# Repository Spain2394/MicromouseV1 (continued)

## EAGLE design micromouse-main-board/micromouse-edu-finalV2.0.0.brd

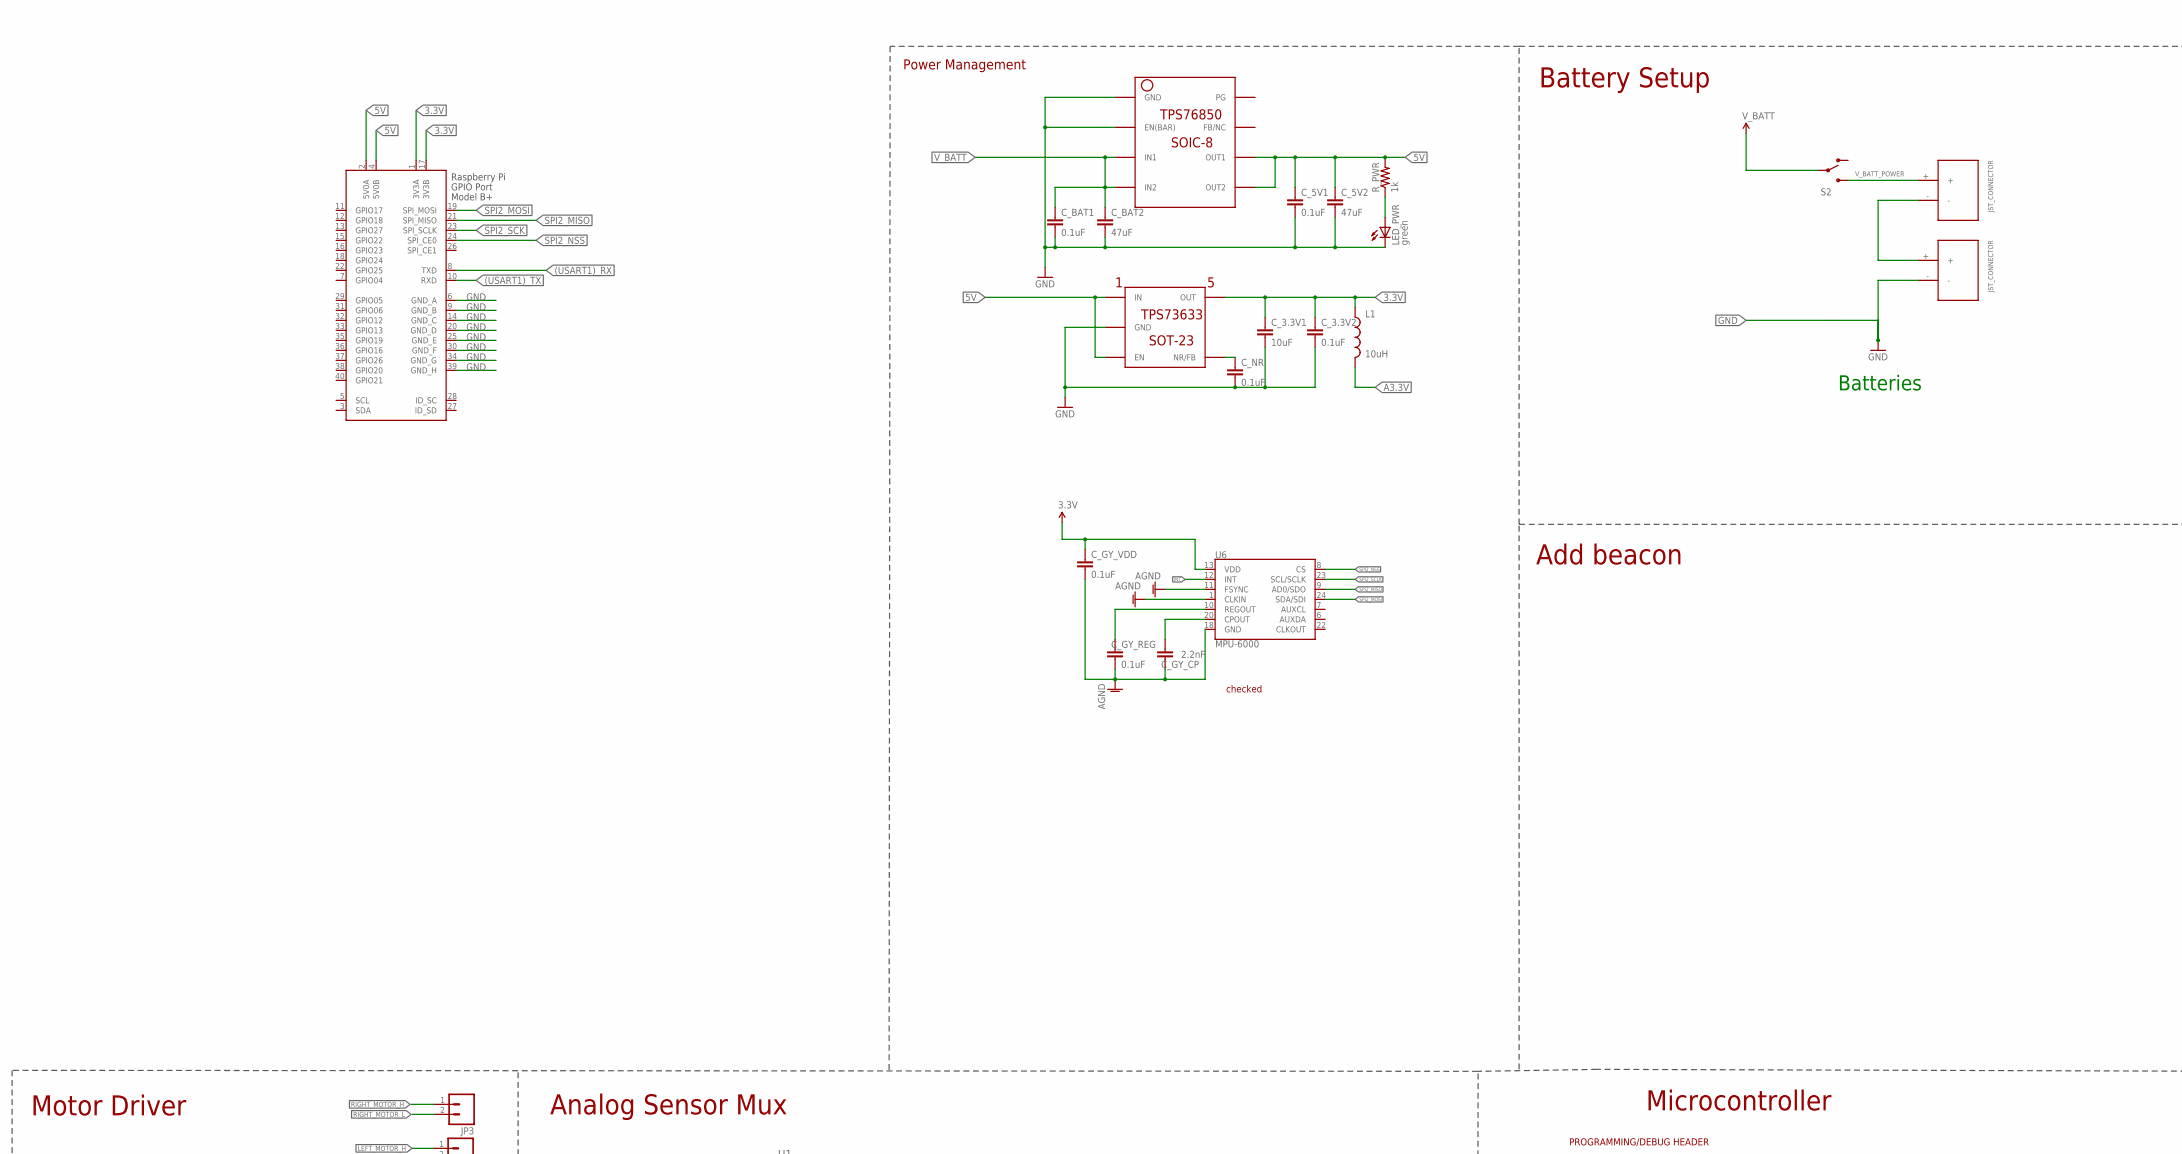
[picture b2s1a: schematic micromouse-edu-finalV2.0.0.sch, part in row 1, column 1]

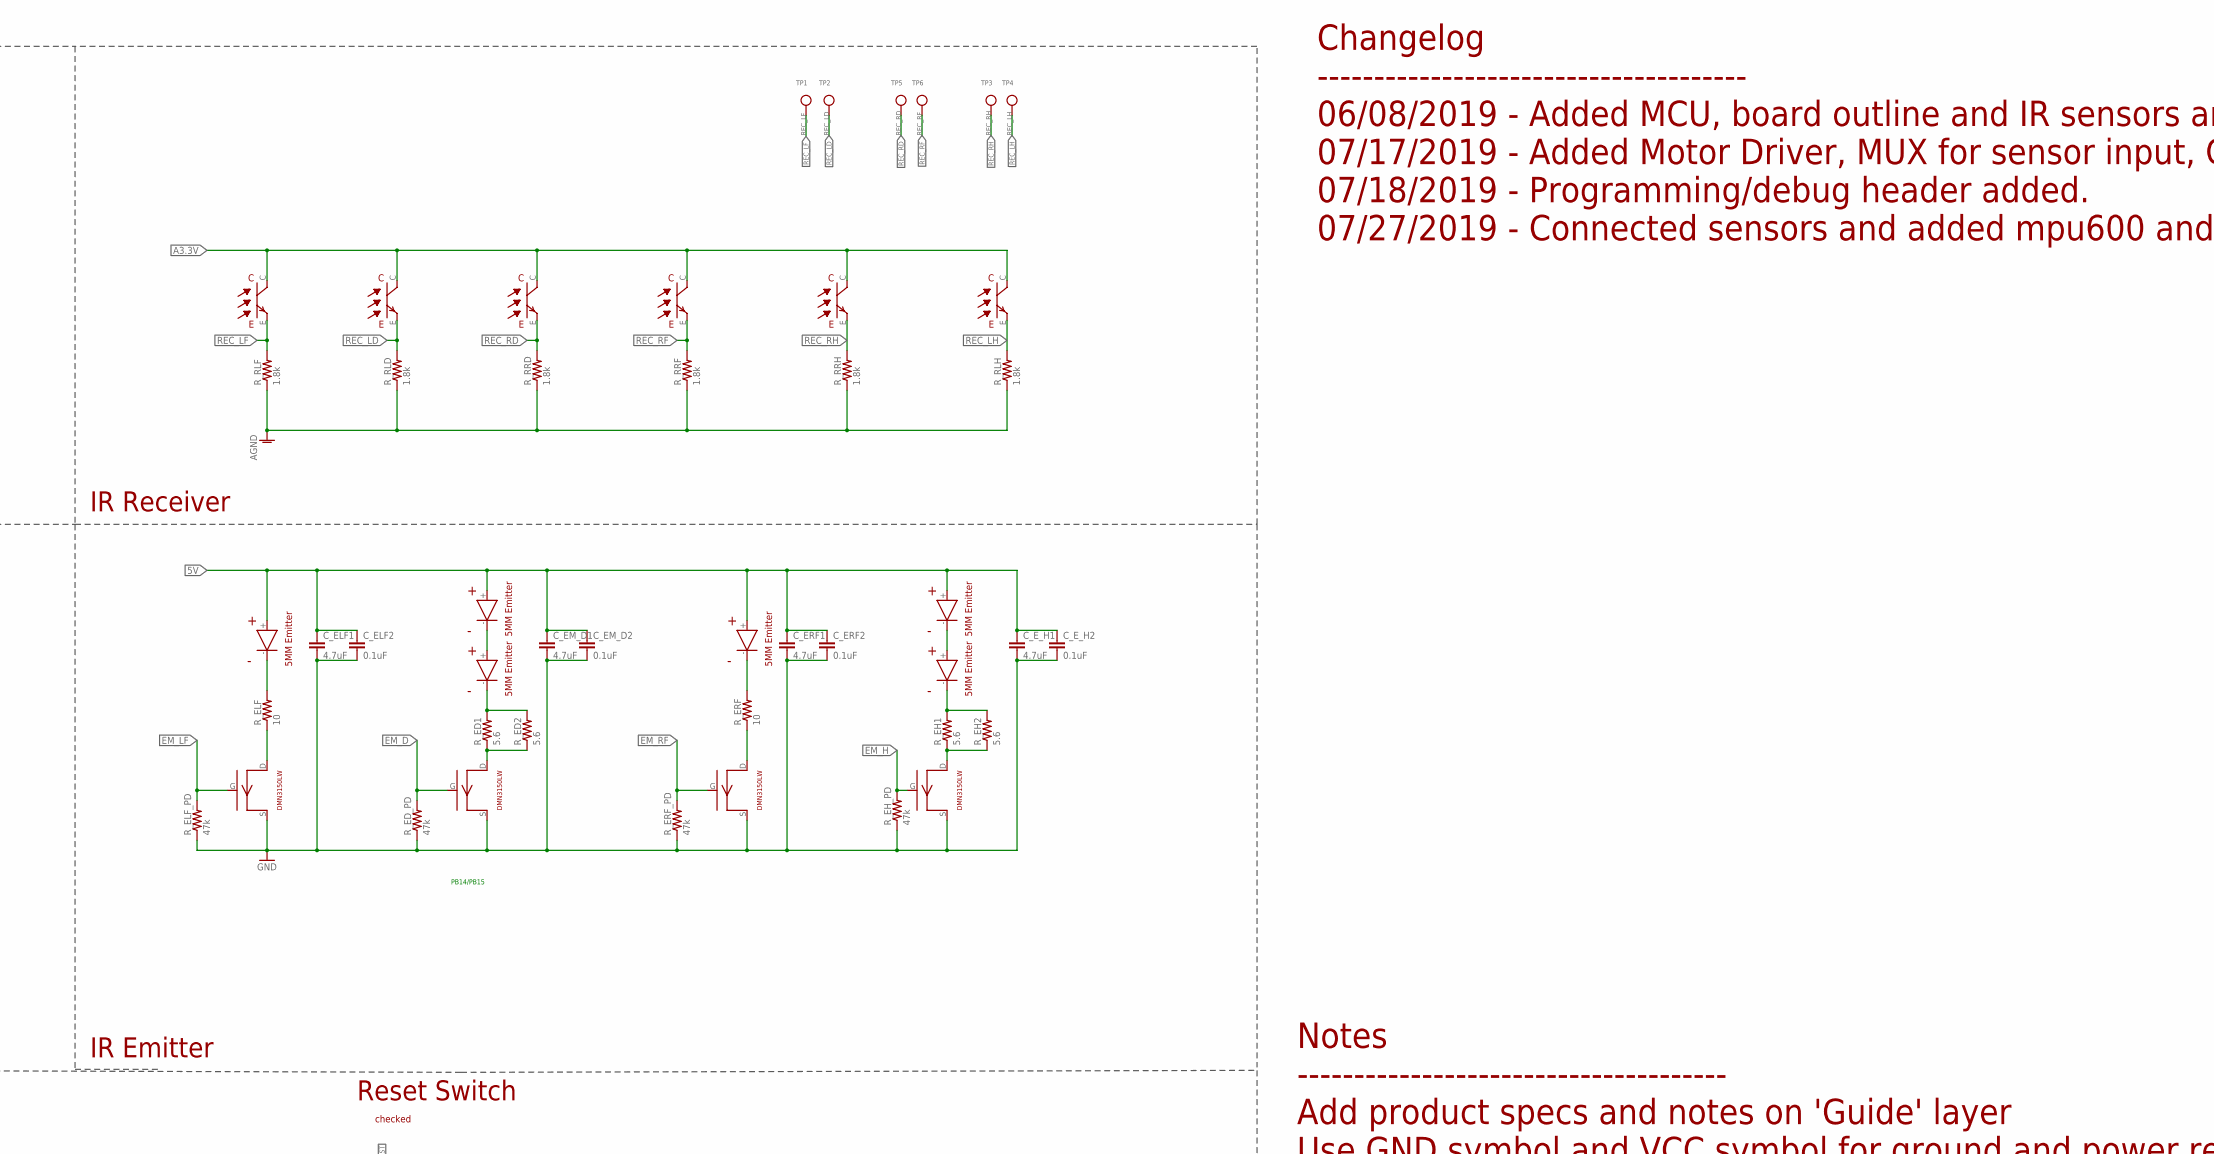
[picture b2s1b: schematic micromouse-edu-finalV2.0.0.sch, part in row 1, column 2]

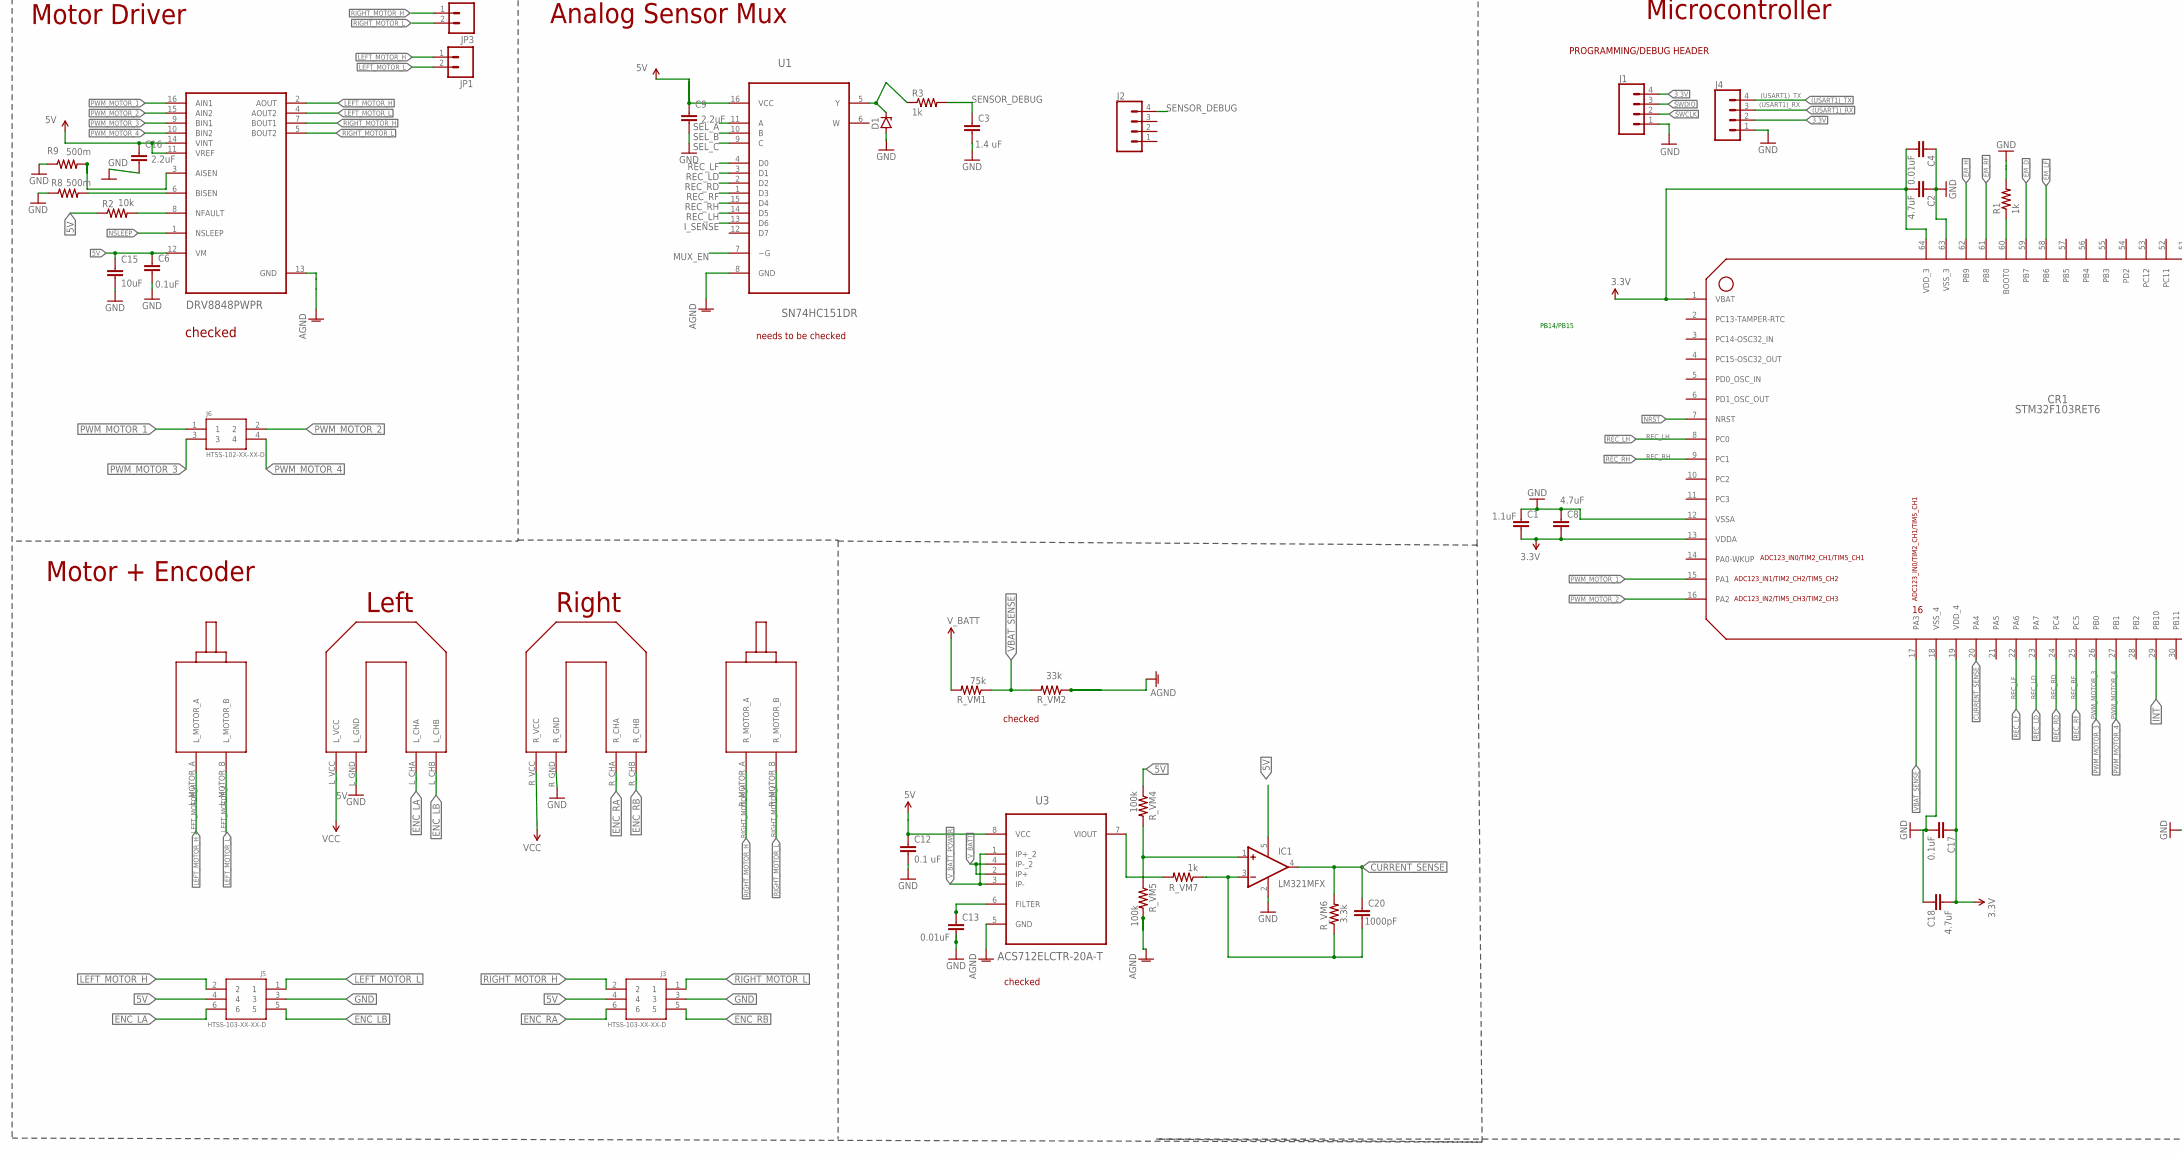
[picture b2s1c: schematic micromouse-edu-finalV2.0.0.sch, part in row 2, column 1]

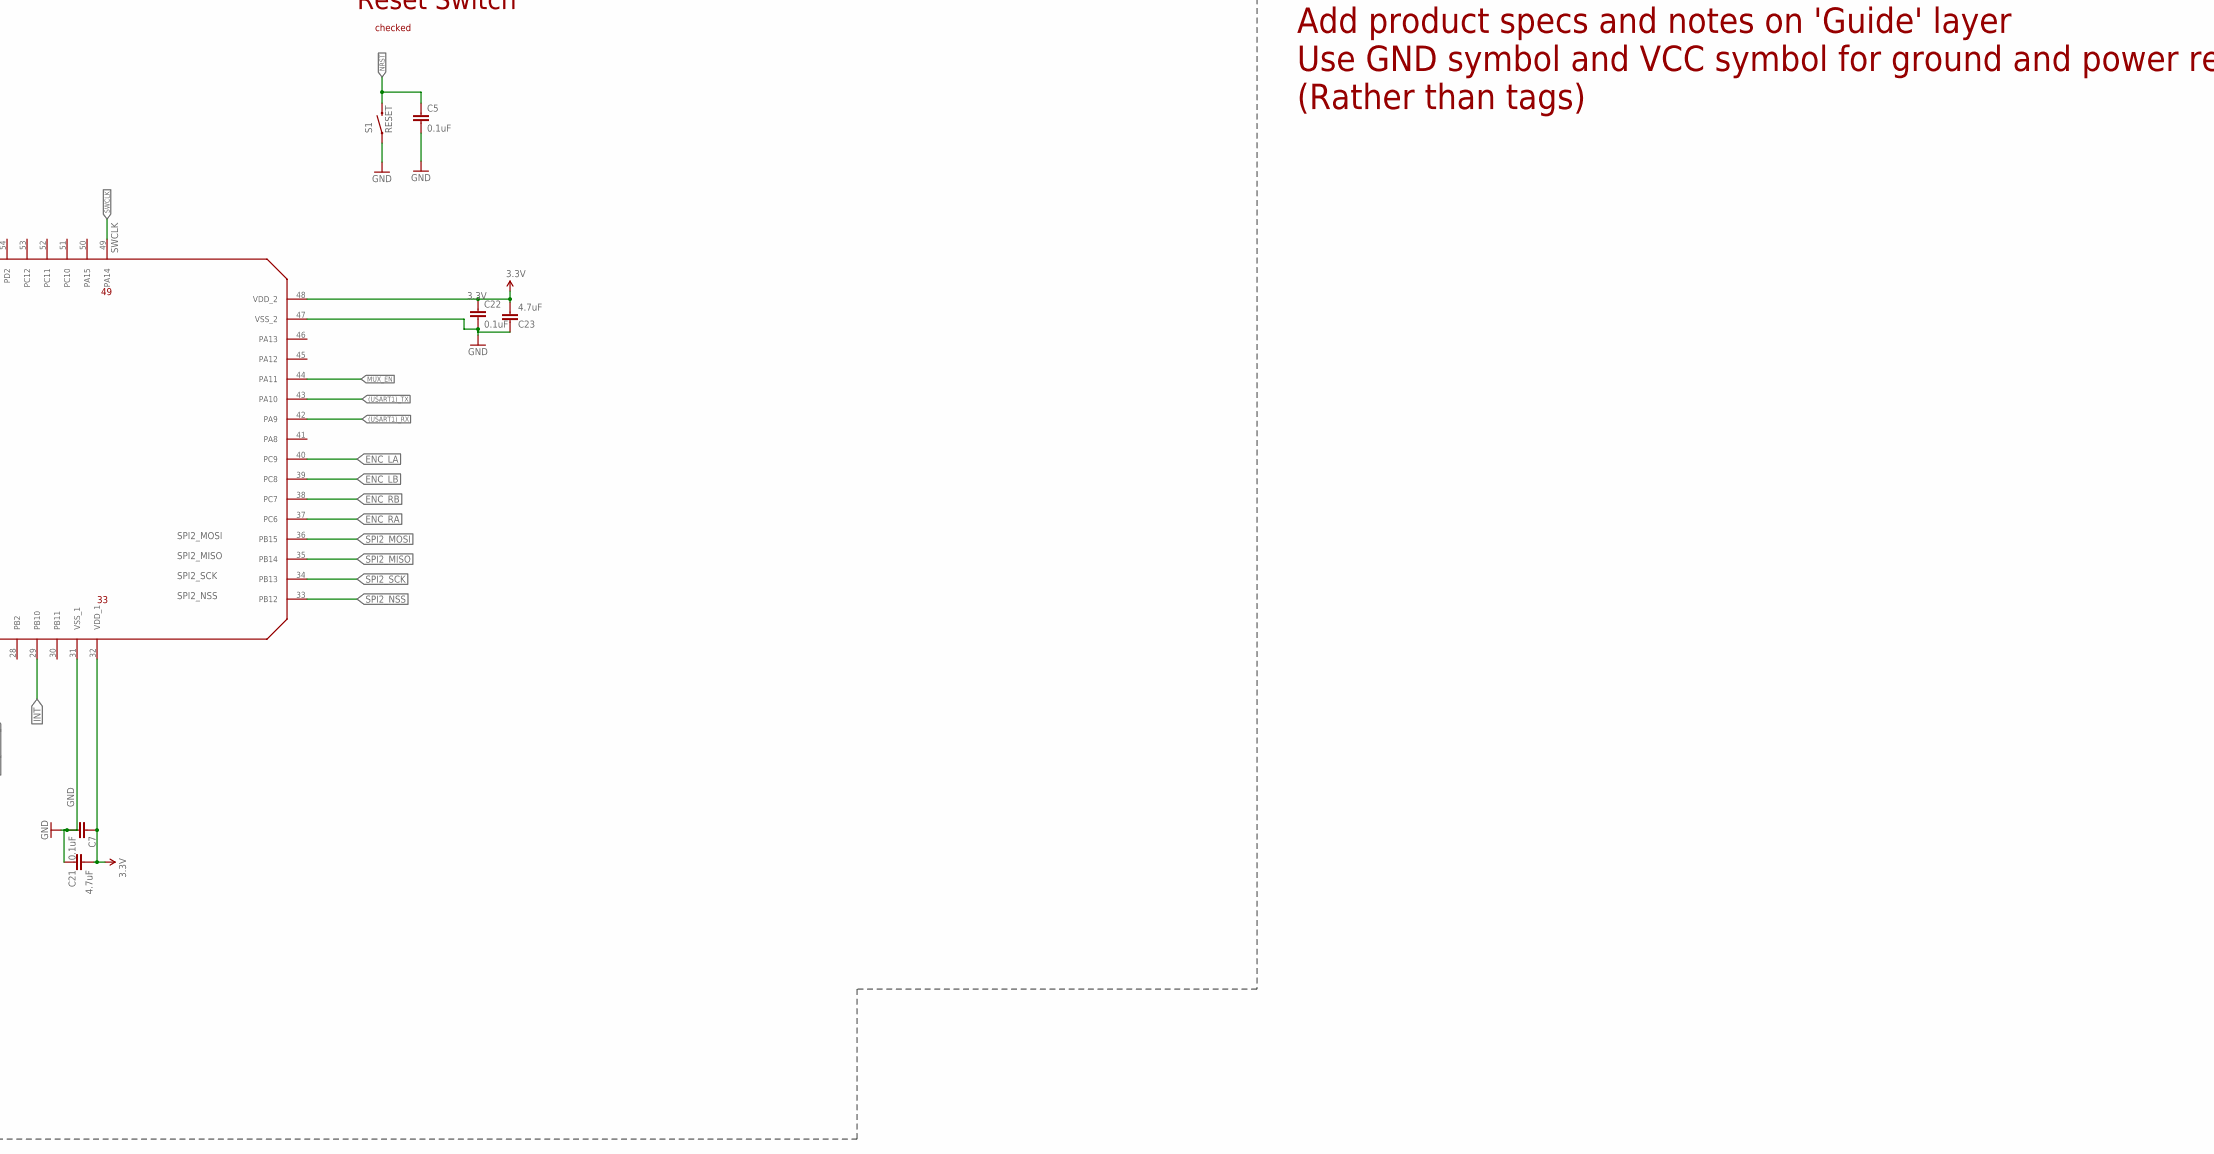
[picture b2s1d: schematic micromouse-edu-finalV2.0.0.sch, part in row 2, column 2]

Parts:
C1: 1.1uF; 0603-CAP
C2, C8, C18, C21, C23: 4.7uF; 0603-CAP
C3: 1.4 uF; 0603-CAP
C4, C13: 0.01uF; 0603-CAP
C5, C6, C7, C17, C22: 0.1uF; 0603-CAP
C9, C16: 2.2uF; 0603-CAP
C12: 0.1 uF; 0603-CAP
C15: 10uF; 0603-CAP
C20: 1000pF; 0603-CAP
CR1: STM32F103RET6; LQFP-64
C_3.3V1: 10uF; 0603-CAP
C_3.3V2, C_5V1: 0.1uF; 0603-CAP
C_5V2: 47uF; 1210
C_BAT1: 0.1uF; 0603-CAP
C_BAT2: 47uF; 1210
C_ELF1: 4.7uF; 0603-CAP
C_ELF2: 0.1uF; 0603-CAP
C_EM_D1: 4.7uF; 0603-CAP
C_EM_D2: 0.1uF; 0603-CAP
C_ERF1: 4.7uF; 0603-CAP
C_ERF2: 0.1uF; 0603-CAP
C_E_H1: 4.7uF; 0603-CAP
C_E_H2: 0.1uF; 0603-CAP
C_GY_CP: 2.2nF; 0603-CAP
C_GY_REG: 0.1uF; 0603-CAP
C_GY_VDD: 0.1uF; 0603-CAP
C_NR: 0.1uF; 0603-CAP
D1: ZENER-DIODESOT23; SOT23
IC1: LM321MFX; SOT23-5
J1, J2, J4: CONN_04; 1X04
J3, J5: HTSS-103-XX-XX-D
J6: HTSS-102-XX-XX-D
JP1, JP3: M02POLAR; MOLEX-1X2
L1: 10uH; 1007
LED_PWR: green; LED-1206
LEFT_FRONT_EMITTER: EMITTER
NMOS1, NMOS2, NMOS3, NMOS4: DMN3150LW
R1: 1k; M0805
R2: 10k; 0805
R3: 1k; R0805
R8, R9: 500m; 0805
REC_LF: RECEIVER
R_ED1, R_ED2: 5.6; 0603-RES
R_ED_PD: 47k; 0603-RES
R_EH1, R_EH2: 5.6; 0603-RES
R_EH_PD: 47k; 0603-RES
R_ELF: 10; 0603-RES
R_ELF_PD: 47k; 0603-RES
R_ERF: 10; 0603-RES
R_ERF_PD: 47k; 0603-RES
R_PWR: 1k; 0603-RES
R_RLD: 1.8k; 0603-RES
R_RLF: 1.8k; 0603-RES
R_RLH: 1.8k; 0603-RES
R_RRD: 1.8k; 0603-RES
R_RRF: 1.8k; 0603-RES
R_RRH: 1.8k; 0603-RES
R_VM1: 75k; 0603-RES
R_VM2: 33k; 0603-RES
R_VM4, R_VM5: 100k; 0603-RES
R_VM6: 3.3k; 0603-RES
R_VM7: 1k; 0603-RES
S1: RESET; TACTILE_SWITCH_SMD_4.6X2.8MM
S2: SWITCH-SPSTPTH; SWITCH-SPDT
TP1, TP2, TP3, TP4, TP5, TP6: TESTPOINTROUND2MM; TESTPOINT_ROUND_2MM
U1: SN74HC151DR; SOIC127P600X175-16N
U2: DRV8848PWPR; SOP65P640X120-17N
U3: ACS712ELCTR-20A-T; SOIC127P600X175-8N
U6: MPU-6000; QFN-24-EP
U$1, U$2: JST_CONNECTOR_FEMALE
U$3: TPS73633(SOT-23)
U$4: TPS76850(SOIC-8)
U$7, U$8, U$9, U$20, U$21: RECEIVER
U$11, U$13, U$17, U$18, U$19: EMITTER
U$12: MY_MM_MOTOR_MOUNT
X1: RASPI_GPIO_B+#_PIN; RASPI_GPIO_B+_PIN

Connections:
3.3V: C1.2, C2.2, C4.2, C7.1, C8.2, C17.1, C18.2, C21.2, C22.1, C23.2, CR1.1 (VBAT), CR1.13 (VDDA), CR1.19 (VDD_4), CR1.32 (VDD_1), CR1.48 (VDD_2), CR1.64 (VDD_3), C_3.3V1.1, C_3.3V2.1, C_GY_VDD.1, J1.4, J4.2, L1.1, U6.13 (VDD), U$3.OUT, X1.1 (3V3A), X1.17 (3V3B)
5V: C6.1, C9.1, C12.1, C15.1, C16.1, C_5V1.1, C_5V2.1, C_ELF1.1, C_ELF2.1, C_EM_D1.1, C_EM_D2.1, C_ERF1.1, C_ERF2.1, C_E_H1.1, C_E_H2.1, IC1.5 (V+), J3.4, J5.4, LEFT_FRONT_EMITTER.+, R2.1, R_PWR.2, R_VM4.1, U1.16 (VCC), U2.11 (VREF), U2.12 (VM), U2.14 (VINT), U3.8 (VCC), U$3.EN, U$3.IN, U$4.OUT1, U$4.OUT2, U$11.+, U$12.L_VCC, U$12.R_VCC, U$13.+, U$18.+, X1.2 (5V0A), X1.4 (5V0B)
(USART1)_RX: CR1.42 (PA9), J4.3, X1.8 (TXD)
(USART1)_TX: CR1.43 (PA10), J4.4, X1.10 (RXD)
A3.3V: L1.2, REC_LF.C, U$7.C, U$8.C, U$9.C, U$20.C, U$21.C
AGND: C_GY_CP.2, C_GY_REG.2, C_GY_VDD.2, R_RLD.1, R_RLF.1, R_RLH.1, R_RRD.1, R_RRF.1, R_RRH.1, R_VM2.1, R_VM5.2, U1.8 (GND), U2.13 (GND), U3.5 (GND), U6.1 (CLKIN), U6.11 (FSYNC), U6.18 (GND)
BATT_CONN: U$1.+, U$2.-
CURRENT_SENSE: C20.1, CR1.20 (PA4), IC1.4 (OUT), R_VM6.2
D2_EM: R_ED1.2, R_ED2.2, U$17.-
D_EM: U$11.-, U$17.+
EM_D: CR1.59 (PB7), NMOS2.G, R_ED_PD.2
EM_H: CR1.62 (PB9), NMOS4.G, R_EH_PD.2
EM_LF: CR1.58 (PB6), NMOS1.G, R_ELF_PD.2
EM_RF: CR1.61 (PB8), NMOS3.G, R_ERF_PD.2
ENC_LA: CR1.40 (PC9), J5.6, U$12.L_CHA
ENC_LB: CR1.39 (PC8), J5.5, U$12.L_CHB
ENC_RA: CR1.37 (PC6), J3.6, U$12.R_CHA
ENC_RB: CR1.38 (PC7), J3.5, U$12.R_CHB
GND: C1.1, C2.1, C3.2, C4.1, C5.2, C6.2, C7.2, C8.1, C9.2, C12.2, C13.2, C15.2, C16.2, C17.2, C18.1, C21.1, C22.2, C23.1, CR1.12 (VSSA), CR1.18 (VSS_4), CR1.31 (VSS_1), CR1.47 (VSS_2), CR1.63 (VSS_3), C_3.3V1.2, C_3.3V2.2, C_5V1.2, C_5V2.2, C_BAT1.2, C_BAT2.2, C_ELF1.2, C_ELF2.2, C_EM_D1.2, C_EM_D2.2, C_ERF1.2, C_ERF2.2, C_E_H1.2, C_E_H2.2, C_NR.2, D1.1 (A), IC1.2 (V-), J1.1, J3.3, J4.1, J5.3, LED_PWR.C, NMOS1.S, NMOS2.S, NMOS3.S, NMOS4.S, R1.2, R8.1, R9.1, R_ED_PD.1, R_EH_PD.1, R_ELF_PD.1, R_ERF_PD.1, S1.1, S1.2 (1), U$1.-, U$3.GND, U$4.EN(BAR), U$4.GND, U$12.L_GND, U$12.R_GND, X1.6 (GND_A), X1.9 (GND_B), X1.14 (GND_C), X1.20 (GND_D), X1.25 (GND_E), X1.30 (GND_F), X1.34 (GND_G), X1.39 (GND_H)
H2_EM: R_EH1.2, R_EH2.2, U$19.-
H_EM: U$18.-, U$19.+
INT: CR1.29 (PB10), U6.12 (INT)
I_SENSE: U1.13 (D6)
LEFT_MOTOR_H: J5.2, JP1.1, U2.2 (AOUT), U$12.L_MOTOR_A
LEFT_MOTOR_L: J5.1, JP1.2, U2.4 (AOUT2), U$12.L_MOTOR_B
LF_EM: LEFT_FRONT_EMITTER.-, R_ELF.2
MUX_EN: CR1.44 (PA11), U1.7 (~G)
unnamed: C13.1, U3.6 (FILTER)
unnamed: D1.3 (C), R3.1, U1.5 (Y)
unnamed: NMOS3.D, R_ERF.1
unnamed: NMOS1.D, R_ELF.1
unnamed: CR1.60 (BOOT0), R1.1
unnamed: R2.2, U2.8 (NFAULT)
unnamed: R9.2, U2.3 (AISEN)
unnamed: NMOS2.D, R_ED1.1, R_ED2.1
unnamed: NMOS4.D, R_EH1.1, R_EH2.1
unnamed: R8.2, U2.6 (BISEN)
unnamed: IC1.1 (+IN), R_VM4.2, R_VM5.1
unnamed: R_VM7.2, U3.7 (VIOUT)
unnamed: C_NR.1, U$3.NR/FB
unnamed: LED_PWR.A, R_PWR.1
unnamed: C_GY_REG.1, U6.10 (REGOUT)
unnamed: C_GY_CP.1, U6.20 (CPOUT)
unnamed: C20.2, IC1.3 (-IN), R_VM6.1, R_VM7.1
NRST: C5.1, CR1.7 (NRST), S1.3 (2), S1.4 (2)
NSLEEP: U2.1 (NSLEEP)
PWM_MOTOR_1: CR1.15 (PA1), J6.1, U2.16 (AIN1)
PWM_MOTOR_2: CR1.16 (PA2), J6.2, U2.15 (AIN2)
PWM_MOTOR_3: CR1.26 (PB0), J6.3, U2.9 (BIN1)
PWM_MOTOR_4: CR1.27 (PB1), J6.4, U2.10 (BIN2)
REC_LD: CR1.23 (PA7), R_RLD.2, TP2.P$1, U1.3 (D1), U$7.E
REC_LF: CR1.22 (PA6), REC_LF.E, R_RLF.2, TP1.P$1, U1.4 (D0)
REC_LH: CR1.8 (PC0), R_RLH.2, TP4.P$1, U1.14 (D5), U$21.E
REC_RD: CR1.24 (PC4), R_RRD.2, TP5.P$1, U1.2 (D2), U$8.E
REC_RF: CR1.25 (PC5), R_RRF.2, TP6.P$1, U1.1 (D3), U$9.E
REC_RH: CR1.9 (PC1), R_RRH.2, TP3.P$1, U1.15 (D4), U$20.E
RF_EM: R_ERF.2, U$13.-
RIGHT_MOTOR_H: J3.2, JP3.1, U2.7 (BOUT1), U$12.R_MOTOR_A
RIGHT_MOTOR_L: J3.1, JP3.2, U2.5 (BOUT2), U$12.R_MOTOR_B
SEL_A: U1.11 (A)
SEL_B: U1.10 (B)
SEL_C: U1.9 (C)
SENSOR_DEBUG: C3.1, J2.4, R3.2
SPI2_MISO: CR1.35 (PB14), U6.9 (AD0/SDO), X1.21 (SPI_MISO)
SPI2_MOSI: CR1.36 (PB15), U6.24 (SDA/SDI), X1.19 (SPI_MOSI)
SPI2_NSS: CR1.33 (PB12), U6.8 (CS), X1.24 (SPI_CE0)
SPI2_SCK: CR1.34 (PB13), X1.23 (SPI_SCLK)
SPI2_SCLK: U6.23 (SCL/SCLK)
SWCLK: CR1.49 (PA14), J1.2
SWDIO: J1.3
VBAT_SENSE: CR1.17 (PA3), R_VM1.1, R_VM2.2
V_BATT: C_BAT1.1, C_BAT2.1, R_VM1.2, S2.2, U3.2 (IP+), U3.4 (IP-_2), U$4.IN1, U$4.IN2
V_BATT_POWER: S2.3 (S), U3.1 (IP+_2), U3.3 (IP-), U$2.+

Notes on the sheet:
Changelog -------------------------------------- 06/08/2019 - Added MCU, board outline and IR sensors and receivers. 07/17/2019 - Added Motor Driver, MUX for sensor input, Current Sensor, picked GPIO to use for MUX select, picked ADC in to route MUX to. 07/18/2019 - Programming/debug header added. 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
Notes -------------------------------------- Add product specs and notes on 'Guide' layer Use GND symbol and VCC symbol for ground and power respectively. (Rather than tags)
PROGRAMMING/DEBUG HEADER
Microcontroller
Reset Switch
Motor + Encoder
Motor Driver
IR Emitter
IR Receiver
Add beacon
Analog Sensor Mux
Batteries
Battery Setup
ADC123_IN0/TIM2_CH1/TIM5_CH1
ADC123_IN1/TIM2_CH2/TIM5_CH2
ADC123_IN2/TIM5_CH3/TIM2_CH3
checked
PB14/PB15
Power Management
needs to be checked
33k

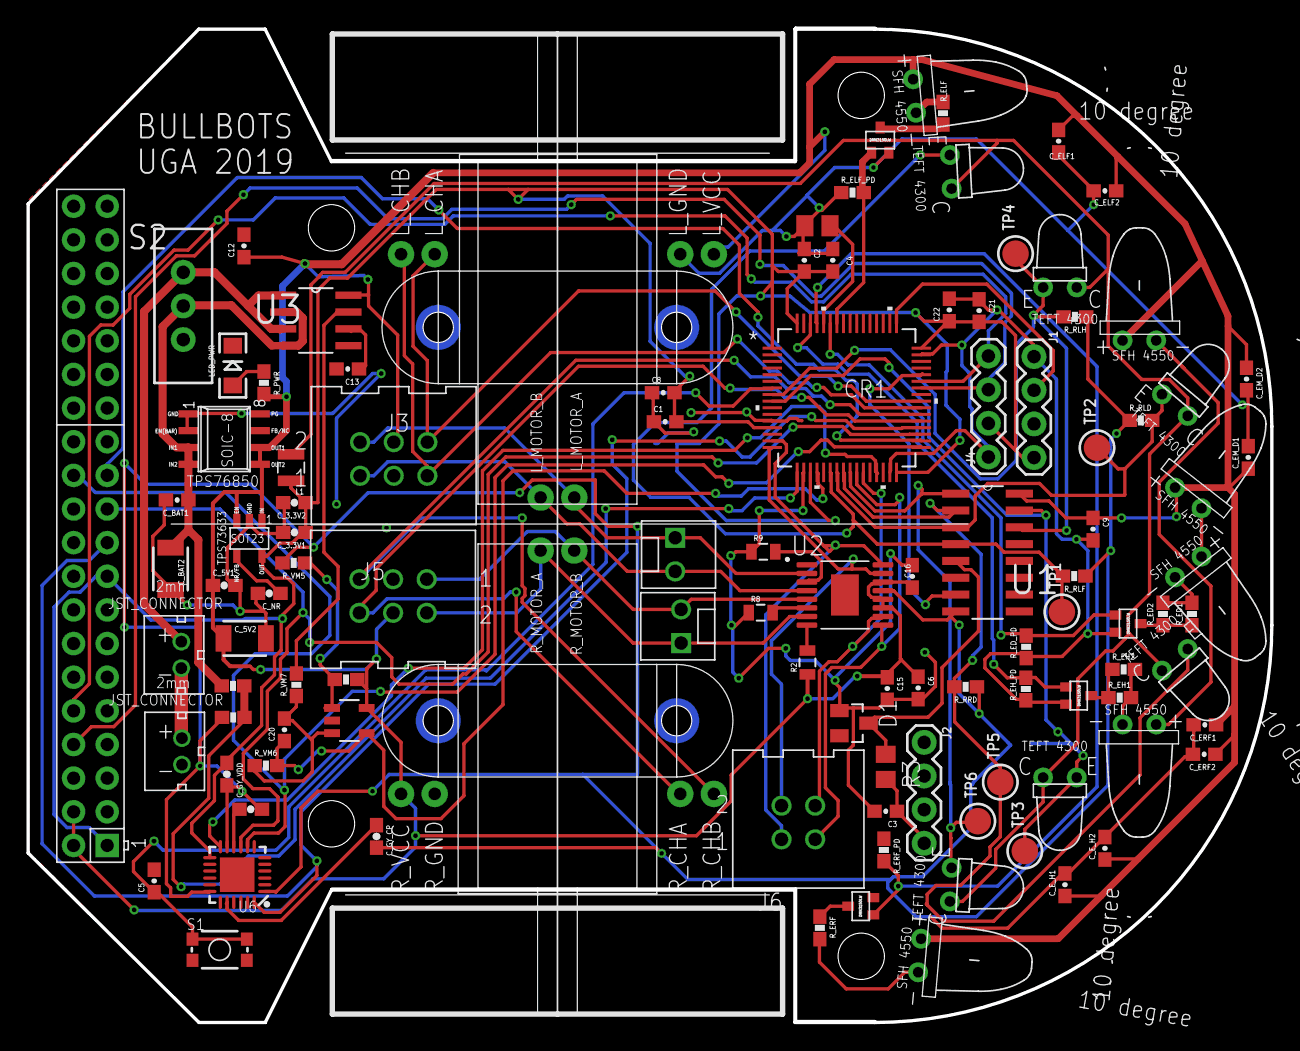
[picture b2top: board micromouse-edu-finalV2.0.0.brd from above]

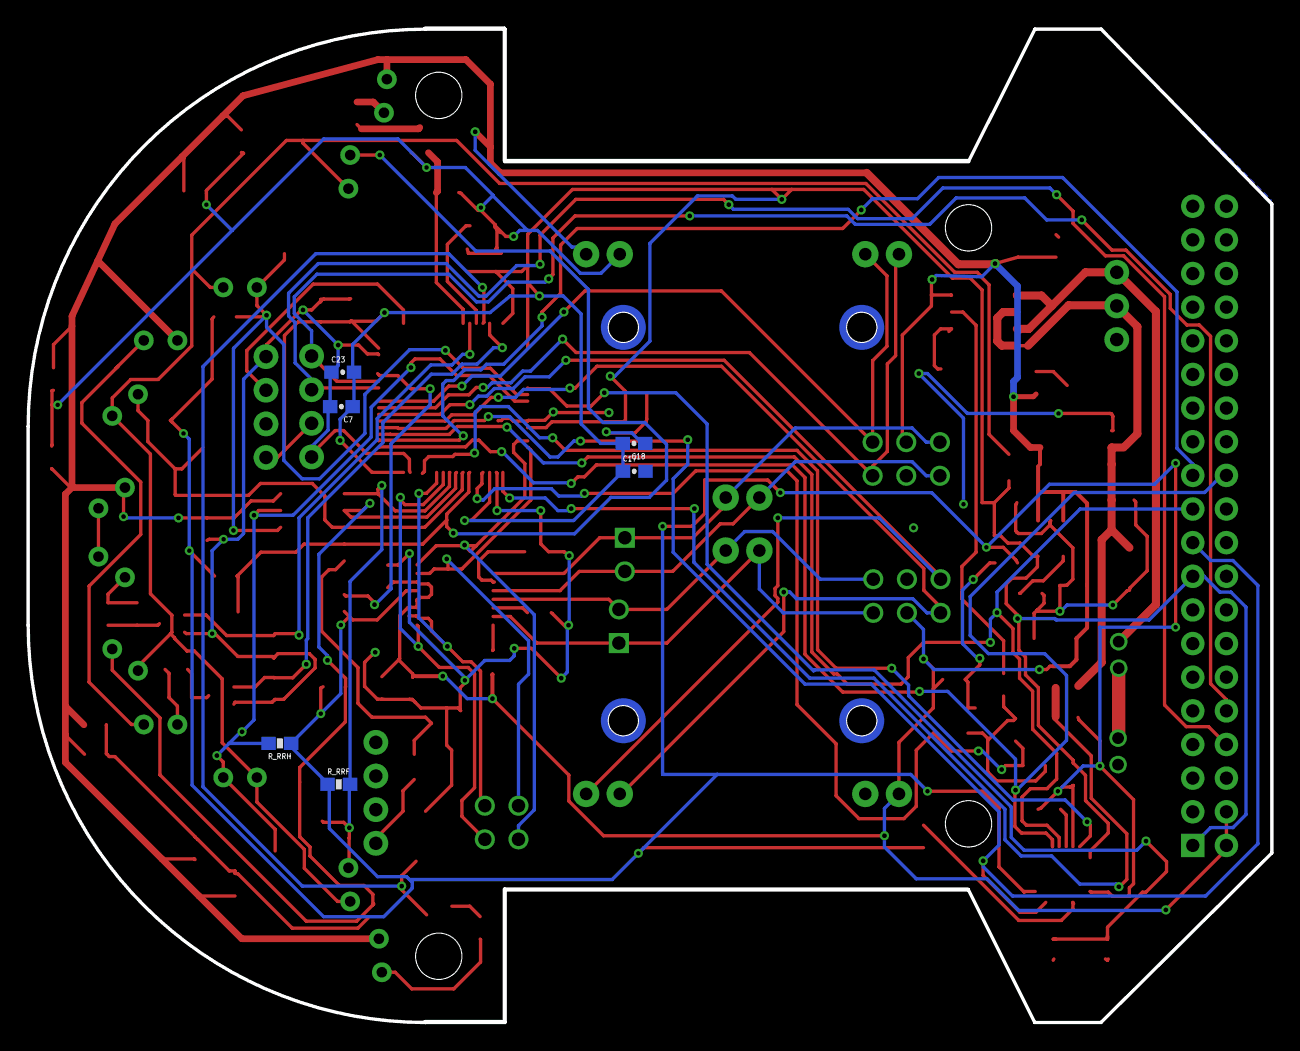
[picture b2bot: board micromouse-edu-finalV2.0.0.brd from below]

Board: 2 copper layers, 93.9 x 75.0 mm, 112 parts (6 on the bottom side), 66 nets.

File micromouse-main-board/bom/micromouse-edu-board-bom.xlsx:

Part | Value | Device | Package | Description | AVAILABILITY | DESCRIPTION | MANUFACTURER_PART_NUMBER | MF | MP | PACKAGE | PRICE | PROD_ID | SF_ID | SPICEPREFIX | VENDOR
C1 | 1.1uF | CAP0603-CAP | 0603-CAP | Capacitor
C2 | 4.7uF | CAP0603-CAP | 0603-CAP | Capacitor
C3 | 1.4 uF | CAP0603-CAP | 0603-CAP | Capacitor
C4 | 0.01uF | CAP0603-CAP | 0603-CAP | Capacitor
C5 | 0.1uF | CAP0603-CAP | 0603-CAP | Capacitor
C6 | 0.1uF | CAP0603-CAP | 0603-CAP | Capacitor
C7 | 0.1uF | CAP0603-CAP | 0603-CAP | Capacitor
C8 | 4.7uF | CAP0603-CAP | 0603-CAP | Capacitor
C9 | 2.2uF | CAP0603-CAP | 0603-CAP | Capacitor
C12 | 0.1 uF | CAP0603-CAP | 0603-CAP | Capacitor
C13 | 0.01uF | CAP0603-CAP | 0603-CAP | Capacitor
C15 | 10uF | CAP0603-CAP | 0603-CAP | Capacitor
C16 | 2.2uF | CAP0603-CAP | 0603-CAP | Capacitor
C17 | 0.1uF | CAP0603-CAP | 0603-CAP | Capacitor
C18 | 4.7uF | CAP0603-CAP | 0603-CAP | Capacitor
C20 | 1000pF | CAP0603-CAP | 0603-CAP | Capacitor
C21 | 4.7uF | CAP0603-CAP | 0603-CAP | Capacitor
C22 | 0.1uF | CAP0603-CAP | 0603-CAP | Capacitor
C23 | 4.7uF | CAP0603-CAP | 0603-CAP | Capacitor
CR1 | STM32F103RET6 | STM32F103RET6 | LQFP-64 |  |  |  | STM32F103RET6 |  |  |  |  |  |  |  | STMicroelectronics
C_3.3V1 | 10uF | CAP0603-CAP | 0603-CAP | Capacitor
C_3.3V2 | 0.1uF | CAP0603-CAP | 0603-CAP | Capacitor
C_5V1 | 0.1uF | CAP0603-CAP | 0603-CAP | Capacitor
C_5V2 | 47uF | CAP1210 | 1210 | Capacitor
C_BAT1 | 0.1uF | CAP0603-CAP | 0603-CAP | Capacitor
C_BAT2 | 47uF | CAP1210 | 1210 | Capacitor
C_ELF1 | 4.7uF | CAP0603-CAP | 0603-CAP | Capacitor
C_ELF2 | 0.1uF | CAP0603-CAP | 0603-CAP | Capacitor
C_EM_D1 | 4.7uF | CAP0603-CAP | 0603-CAP | Capacitor
C_EM_D2 | 0.1uF | CAP0603-CAP | 0603-CAP | Capacitor
C_ERF1 | 4.7uF | CAP0603-CAP | 0603-CAP | Capacitor
C_ERF2 | 0.1uF | CAP0603-CAP | 0603-CAP | Capacitor
C_E_H1 | 4.7uF | CAP0603-CAP | 0603-CAP | Capacitor
C_E_H2 | 0.1uF | CAP0603-CAP | 0603-CAP | Capacitor
C_GY_CP | 2.2nF | CAP0603-CAP | 0603-CAP | Capacitor
C_GY_REG | 0.1uF | CAP0603-CAP | 0603-CAP | Capacitor
C_GY_VDD | 0.1uF | CAP0603-CAP | 0603-CAP | Capacitor
C_NR | 0.1uF | CAP0603-CAP | 0603-CAP | Capacitor
D1 |  | ZENER-DIODESOT23 | SOT23 | Z-Diode
IC1 | LM321MFX | LM321MFX | SOT23-5 | Low Power Single Op Amp
J1 |  | CONN_04 | 1X04 | Multi connection point. Often used as Generic Header-pin footprint for 0.1 inch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 |  |  |  |  |  |  |  | CONN-09696
J2 |  | CONN_04 | 1X04 | Multi connection point. Often used as Generic Header-pin footprint for 0.1 inch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 |  |  |  |  |  |  |  | CONN-09696
J3 | HTSS-103-XX-XX-D | HTSS-103-XX-XX-D | HTSS-103-XX-XX-D | HIGH TEMP TOP SHROUD TERMINAL STRIP.
J4 |  | CONN_04 | 1X04 | Multi connection point. Often used as Generic Header-pin footprint for 0.1 inch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 |  |  |  |  |  |  |  | CONN-09696
J5 | HTSS-103-XX-XX-D | HTSS-103-XX-XX-D | HTSS-103-XX-XX-D | HIGH TEMP TOP SHROUD TERMINAL STRIP.
J6 | HTSS-102-XX-XX-D | HTSS-102-XX-XX-D | HTSS-102-XX-XX-D | HIGH TEMP TOP SHROUD TERMINAL STRIP.
J7 | HTSS-102-XX-XX-D | HTSS-102-XX-XX-D | HTSS-102-XX-XX-D | HIGH TEMP TOP SHROUD TERMINAL STRIP.
JP1 |  | M02POLAR | MOLEX-1X2 | Header 2
JP3 |  | M02POLAR | MOLEX-1X2 | Header 2
L1 | 10uH | INDUCTOR1007 | 1007 | Inductors
LED_PWR | green | LED1206 | LED-1206 | LEDs
LEFT_FRONT_EMITTER | EMITTER | EMITTER | EMITTER
NMOS1 | DMN3150LW | DMN3150LW | DMN3150LW
NMOS2 | DMN3150LW | DMN3150LW | DMN3150LW
NMOS3 | DMN3150LW | DMN3150LW | DMN3150LW
NMOS4 | DMN3150LW | DMN3150LW | DMN3150LW
R1 | 1k | R-US_M0805 | M0805 | RESISTOR
R2 | 10k | RESISTOR0805-RES | 805 | Resistor
R3 | 1k | R-US_R0805 | R0805 | RESISTOR
R8 | 500m | RESISTOR0805-RES | 805 | Resistor
R9 | 500m | RESISTOR0805-RES | 805 | Resistor
REC_LF | RECEIVER | RECEIVER | RECEIVER
R_ED1 | 5.6 | RESISTOR0603-RES | 0603-RES | Resistor
R_ED2 | 5.6 | RESISTOR0603-RES | 0603-RES | Resistor
R_ED_PD | 47k | RESISTOR0603-RES | 0603-RES | Resistor
R_EH1 | 5.6 | RESISTOR0603-RES | 0603-RES | Resistor
R_EH2 | 5.6 | RESISTOR0603-RES | 0603-RES | Resistor
R_EH_PD | 47k | RESISTOR0603-RES | 0603-RES | Resistor
R_ELF | 10 | RESISTOR0603-RES | 0603-RES | Resistor
R_ELF_PD | 47k | RESISTOR0603-RES | 0603-RES | Resistor
R_ERF | 10 | RESISTOR0603-RES | 0603-RES | Resistor
R_ERF_PD | 47k | RESISTOR0603-RES | 0603-RES | Resistor
R_PWR | 1k | RESISTOR0603-RES | 0603-RES | Resistor
R_RLD | 1.8k | RESISTOR0603-RES | 0603-RES | Resistor
R_RLF | 1.8k | RESISTOR0603-RES | 0603-RES | Resistor
R_RLH | 1.8k | RESISTOR0603-RES | 0603-RES | Resistor
R_RRD | 1.8k | RESISTOR0603-RES | 0603-RES | Resistor
R_RRF | 1.8k | RESISTOR0603-RES | 0603-RES | Resistor
R_RRH | 1.8k | RESISTOR0603-RES | 0603-RES | Resistor
R_VM1 | 75k | RESISTOR0603-RES | 0603-RES | Resistor
R_VM2 | 25k | RESISTOR0603-RES | 0603-RES | Resistor
R_VM4 | 100k | RESISTOR0603-RES | 0603-RES | Resistor
R_VM5 | 100k | RESISTOR0603-RES | 0603-RES | Resistor
R_VM6 | 3.3k | RESISTOR0603-RES | 0603-RES | Resistor
R_VM7 | 1k | RESISTOR0603-RES | 0603-RES | Resistor
S1 | RESET | SWITCH-MOMENTARY-2SMD-4.6X2.8MM | TACTILE_SWITCH_SMD_4.6X2.8MM | Various NO switches- pushbuttons
S2 |  | SWITCH-SPSTPTH | SWITCH-SPDT | SPST Switch
TP1 |  | TESTPOINTROUND2MM | TESTPOINT_ROUND_2MM | Test Point
TP2 |  | TESTPOINTROUND2MM | TESTPOINT_ROUND_2MM | Test Point
TP3 |  | TESTPOINTROUND2MM | TESTPOINT_ROUND_2MM | Test Point
TP4 |  | TESTPOINTROUND2MM | TESTPOINT_ROUND_2MM | Test Point
TP5 |  | TESTPOINTROUND2MM | TESTPOINT_ROUND_2MM | Test Point
TP6 |  | TESTPOINTROUND2MM | TESTPOINT_ROUND_2MM | Test Point
U$1 | JST_CONNECTOR_FEMALE | JST_CONNECTOR_FEMALE | JST_CONNECTOR_FEMALE
U$2 | JST_CONNECTOR_FEMALE | JST_CONNECTOR_FEMALE | JST_CONNECTOR_FEMALE
U$3 | TPS73633(SOT-23) | TPS73633(SOT-23) | TPS73633(SOT-23)
U$4 | TPS76850(SOIC-8) | TPS76850(SOIC-8) | TPS76850(SOIC-8)
U$7 | RECEIVER | RECEIVER | RECEIVER
U$8 | RECEIVER | RECEIVER | RECEIVER
U$9 | RECEIVER | RECEIVER | RECEIVER
U$11 | EMITTER | EMITTER | EMITTER
U$12 | MY_MM_MOTOR_MOUNT | MY_MM_MOTOR_MOUNT | MY_MM_MOTOR_MOUNT
U$13 | EMITTER | EMITTER | EMITTER
U$17 | EMITTER | EMITTER | EMITTER
U$18 | EMITTER | EMITTER | EMITTER
U$19 | EMITTER | EMITTER | EMITTER
U$20 | RECEIVER | RECEIVER | RECEIVER
U$21 | RECEIVER | RECEIVER | RECEIVER
U1 | SN74HC151DR | SN74HC151DR | SOIC127P600X175-16N | 8-Line to 1-Line Dataselectors /MultiPlexers | Unavailable | 8-Line To 1-Line Data Selectors/Multiplexers 16-SOIC -40 to 85 |  | Texas Instruments | SN74HC151DR | SOIC-16 Texas Instruments | None
U2 | DRV8848PWPR | DRV8848PWPR | SOP65P640X120-17N | None | Unavailable | 2A Dual H-Bridge Motor Driver _PWM Control_ 16-HTSSOP -40 to 85 |  | Texas Instruments | DRV8848PWPR | HTSSOP-16 Texas Instruments | None
U3 | ACS712ELCTR-20A-T | ACS712ELCTR-20A-T | SOIC127P600X175-8N | Linear Current Sensor | Unavailable | Fully Integrated
U6 | MPU-6000 | MPU-6000 | QFN-24-EP | Invensense MPU-6000 6-Axis Gryoscope/Accelerometer |  |  |  |  |  |  |  | IC-11089 | SEN-11234
X1 | RASPI_GPIO_B+#_PIN | RASPI_GPIO_B+#_PIN | RASPI_GPIO_B+_PIN | 2x20 header connector

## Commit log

2019-06-20 Add files via upload
    Build schems from this file. Only includes STM32 processor. Needs power system, motor system, interface for flashing, interface for adding layers, etc.
2019-06-20 organize file structure
2019-07-07 added git ignore
2019-07-08 creating wiki template
2019-07-08 edited readme
2019-07-08 added wiki, modified micromouse board layout
2019-07-08 updated readme links
2019-07-08 added more links
2019-07-08 more links
2019-07-08 got board outline to work
2019-07-08 organizational stuff
2019-07-09 updated board
2019-07-11 added part to optional parts list
2019-07-11 updated BOM
2019-07-12 added mpu dev board
2019-07-18 cleaned repo for testing post
2019-07-18 Added debug header
2019-07-23 added software repo, schematic not complete
2019-07-23 adding submodule
2019-07-31 circuits are there power regulators may need to change, still need to set up the analog power nets
2019-07-31 eagle schematic was broken, replaced with bckup
2019-07-31 gitignore files
2019-08-15 asdf
2019-08-15 this one works
2019-08-15 changed decoupling caps
2019-08-21 modified ground concept, ran error check
2019-08-21 gnd concept, and ran error check
2019-08-21 removed weird version name
2019-08-21 added sensor output from mux to generic header. Included RC circuit as well.
2019-08-23 added blue pill pinout
2019-08-23 added bluepill pinout
2019-09-01 made makefile more robust
2019-09-14 Update README.md
    3d model
2019-09-14 added 3d models for dc motors, updated bom with new encoders and dc motors
2019-09-15 update Green Giant ref link
2019-09-15 updated bom to reflect motor quotes
2019-10-01 3D board model added to 3D models
2019-10-02 added docs
2019-10-02 added bom for edu micromouse
2019-10-02 submodule yeah or nah
2019-10-02 added submodule
2019-10-02 ignore .gimodules
2019-10-02 you need to keep that
2019-10-03 added updated bom and changed some board components,these few traces will still need to be routed
2019-10-17 edu finalized
2019-10-21 finalized micromouse edu with raspi header, includes gerber files
2019-10-28 added 3d models
2019-10-28 added images
2019-10-29 added 3d model images
2019-11-16 value update to reflect bom
2020-01-22 reorganized
2020-01-23 Add files via upload
    Added i2c to mpu, added swdio, added switch for changing modes, added ground plane, added agnd plane, routed swdio, changed and routed usart tx and rx.
2020-01-26 new layout
2020-02-03 power reg. added placement done
2020-02-16 planes seem to be layed nicely
2020-02-19 board finalized
2020-02-19 added cam processor and gerbers
2020-02-21 added complete bom, modified board parts based on part availability
2020-04-16 add gitignore
2020-06-14 remove garbage
2020-06-14 clean garbage
2020-06-14 rearrange
2020-10-01 add release bom
